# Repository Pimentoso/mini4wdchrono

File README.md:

# Mini4wdChrono

Mini4wdChrono is a free, open-source desktop application for timing and managing
Mini 4WD races on three-lane Japan Cup tracks. It combines Arduino-based lap
detection with an interface designed for race organizers and large-screen displays.

## Features

- Live timing for up to three lanes, including position, gaps, average speed, and split times
- Configurable lap counts, timing thresholds, start sequence, sensors, LEDs, and buzzer
- Track import from [Mini4WD Track Editor](https://mini4wd-track-editor.pimentoso.com/)
- Player and round import from [Mini4WD Tournament Generator](https://mini4wd-tournament.pimentoso.com/)
- Tournament standings, editable results, and free-race support
- Persistent race data and Excel result exports

## Hardware

The hardware is designed to be affordable and straightforward to assemble while
maintaining accurate timing. An Arduino running Firmata connects the sensors and
optional start button, LED strip, and buzzer to the application.

See the project wiki for complete assembly and setup instructions:

- [Required hardware](https://github.com/Pimentoso/mini4wdchrono/wiki/Hardware-parts-needed)
- [Wiring diagrams](https://github.com/Pimentoso/mini4wdchrono/wiki/Hardware-diagrams)
- [Flashing the Arduino](https://github.com/Pimentoso/mini4wdchrono/wiki/Flashing-the-arduino-board)
- [Building the lap timer](https://github.com/Pimentoso/mini4wdchrono/wiki/Lap-timer-building)
- [Launching the software](https://github.com/Pimentoso/mini4wdchrono/wiki/Launching-the-software)

## Download

Download a packaged build for your operating system from the
[GitHub Releases page](https://github.com/Pimentoso/mini4wdchrono/releases).
Available platforms may vary by release.

## Getting started

1. Build and flash the Arduino hardware by following the
   [hardware guides](https://github.com/Pimentoso/mini4wdchrono/wiki).
2. Connect the Arduino to your computer over USB.
3. Launch Mini4wdChrono and open the **Configuration** tab.
4. Select the serial port and configure the sensor pins and any optional hardware.
5. Create a track with
   [Mini4WD Track Editor](https://mini4wd-track-editor.pimentoso.com/) and load its
   link in the race setup screen.
6. For tournament races, create a player list and rounds with
   [Mini4WD Tournament Generator](https://mini4wd-tournament.pimentoso.com/) and
   load its link as well.

For more detail, see the
[software quick-start guide](https://github.com/Pimentoso/mini4wdchrono/wiki/Software-quick-start-guide)
and [tournament rules](https://github.com/Pimentoso/mini4wdchrono/wiki/Software-tournament-rules).

## Screenshots

### Live race view

Position, gap to the leader, average speed, and split times.

### Player standings

Player rankings with each racer's best time highlighted.

### Tournament rounds

An overview of every round with editable results.

### Race setup

Track, tournament, timing, and race-mode configuration.

## Development

Mini4wdChrono requires Node.js 22.13.0 and npm 9 or later. Node.js is managed
with [asdf](https://asdf-vm.com/); install asdf and its Node.js plugin, then
run the following from the repository root to install the pinned version:

```bash
asdf plugin add nodejs
asdf install
```

Use the setup instructions for your operating system before installing the
project.

### Set up macOS

Install the Xcode Command Line Tools, then install
[Homebrew](https://brew.sh/) if it is not already available:

```bash
xcode-select --install
```

After the Command Line Tools installation completes, use Homebrew to install
Git and the Arduino IDE:

```bash
brew install git
brew install --cask arduino-ide
```

### Set up Windows

Run the following commands from an elevated PowerShell window. They install Git,
Python, the Visual C++ build tools required by native dependencies, and the
Arduino IDE:

```powershell
winget install --id Git.Git --exact --accept-package-agreements --accept-source-agreements
winget install --id Python.Python.3.11 --exact --accept-package-agreements --accept-source-agreements
winget install --id Microsoft.VisualStudio.2022.BuildTools --exact `
  --accept-package-agreements --accept-source-agreements `
  --override "--wait --passive --add Microsoft.VisualStudio.Workload.VCTools --includeRecommended"
winget install --id ArduinoSA.IDE.stable --exact --accept-package-agreements --accept-source-agreements
winget install --id OpenJS.NodeJS.22 --exact --accept-package-agreements --accept-source-agreements
```

Close and reopen PowerShell after the installations finish so the new commands
are available on `PATH`.

### Set up Linux

The following commands prepare an Ubuntu or Debian system. They install the
compiler toolchain, Git, and zip:

```bash
sudo apt update
sudo apt install -y build-essential ca-certificates curl git zip
sudo usermod -aG dialout "$USER"
```

Sign out and back in after adding your account to the `dialout` group. This
allows Mini4wdChrono to access the Arduino serial port without making the device
world-writable. Install the [Arduino IDE](https://www.arduino.cc/en/software)
from Arduino's official download if you need to flash the board.

For other Linux distributions, install equivalent packages with the system's
package manager.

### Install and run Mini4wdChrono

After preparing the operating system, clone the repository, install the locked
dependencies, and start Electron:

```bash
git clone https://github.com/Pimentoso/mini4wdchrono.git
cd mini4wdchrono
npm ci
npm start
```

Connect a Firmata-compatible Arduino over USB to test hardware integration.
Use `npm run watch` to reload the application while developing. Run the linter
before submitting changes:

```bash
npm run lint:fix
npm run lint
```

### Project structure

- `window.js` — Electron main process, persistence, serial hardware, and IPC
- `preload.js` — restricted renderer-facing IPC API
- `js/` — renderer UI and race-management logic
- `index.html` — application markup
- `utils/` — release packaging scripts

## Building release artifacts

The build scripts install the locked dependencies, package the application, and
create a zip file in `release-builds/`.

| Platform | Command | Output |
| --- | --- | --- |
| macOS x64 | `./utils/build-darwin.sh` | `Mini4wdChrono-mac-x64.zip` |
| Linux x64 | `./utils/build-linux-x64.sh` | `Mini4wdChrono-linux-x64.zip` |
| Windows x64 | `.\utils\build-win64.ps1` | `Mini4wdChrono-windows-x64.zip` |

Run each script on its target operating system. Cross-platform packaging is not
supported by these scripts.

## Contributing

Bug reports and pull requests are welcome. Before opening a pull request:

1. Create a focused branch for the change.
2. Keep hardware access in the Electron main process and expose it to the
   renderer through IPC.
3. Run `npm run lint:fix` followed by `npm run lint`.
4. Describe the change, how it was tested, and any hardware used for testing.

Please use [GitHub Issues](https://github.com/Pimentoso/mini4wdchrono/issues) for bugs and feature requests.

## License

Mini4wdChrono is available under the [MIT License](LICENSE).

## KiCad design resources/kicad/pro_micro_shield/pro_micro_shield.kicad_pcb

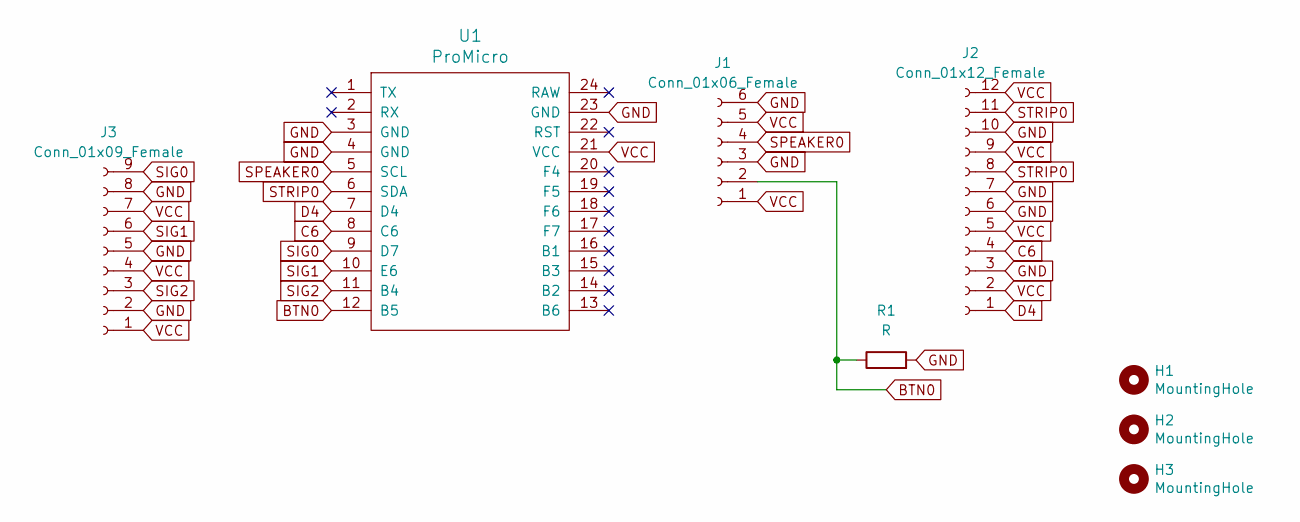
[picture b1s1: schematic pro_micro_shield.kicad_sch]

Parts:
H1, H2, H3: MountingHole; MountingHole_2.2mm_M2
J1: Conn_01x06_Female; PinHeader_1x06_P2.54mm_Vertical
J2: Conn_01x12_Female; PinHeader_1x12_P2.54mm_Vertical
J3: Conn_01x09_Female; PinHeader_1x09_P2.54mm_Vertical
R1: R; R_Axial_DIN0207_L6.3mm_D2.5mm_P15.24mm_Horizontal
U1: ProMicro; ArduinoProMicro

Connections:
BTN0: J1.2, R1.1, U1.12 (B5)
C6: J2.4, U1.8 (C6)
D4: J2.1, U1.7 (D4)
GND: J1.3, J1.6, J2.3, J2.6, J2.7, J2.10, J3.2, J3.5, J3.8, R1.2, U1.3 (GND), U1.4 (GND), U1.23 (GND)
SIG0: J3.9, U1.9 (D7)
SIG1: J3.6, U1.10 (E6)
SIG2: J3.3, U1.11 (B4)
SPEAKER0: J1.4, U1.5 (SCL)
STRIP0: J2.8, J2.11, U1.6 (SDA)
VCC: J1.1, J1.5, J2.2, J2.5, J2.9, J2.12, J3.1, J3.4, J3.7, U1.21 (VCC)

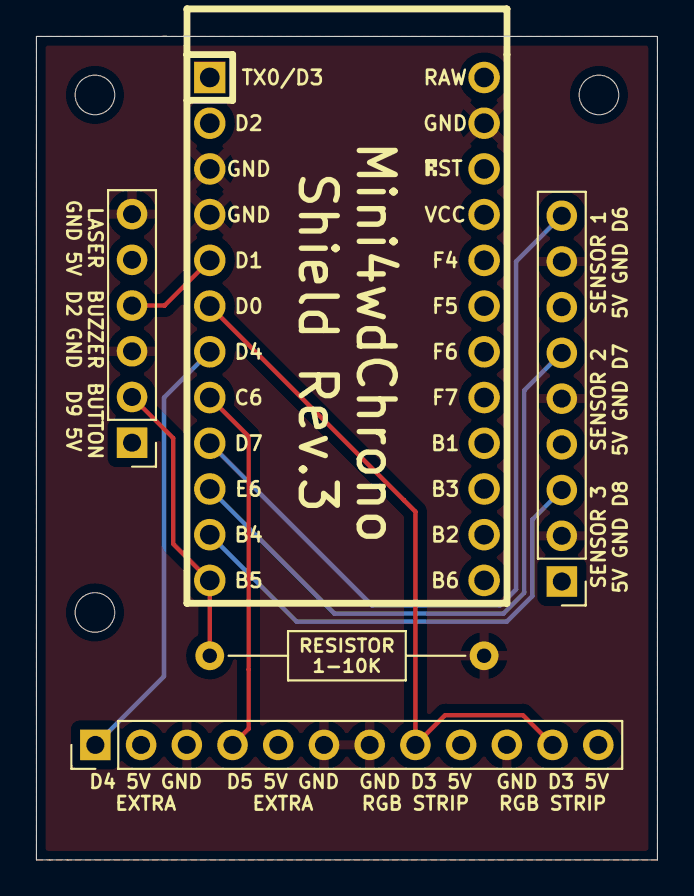
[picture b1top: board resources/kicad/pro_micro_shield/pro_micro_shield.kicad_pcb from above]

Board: 2 copper layers, 34.5 x 45.8 mm, 8 parts (0 on the bottom side), 10 nets.

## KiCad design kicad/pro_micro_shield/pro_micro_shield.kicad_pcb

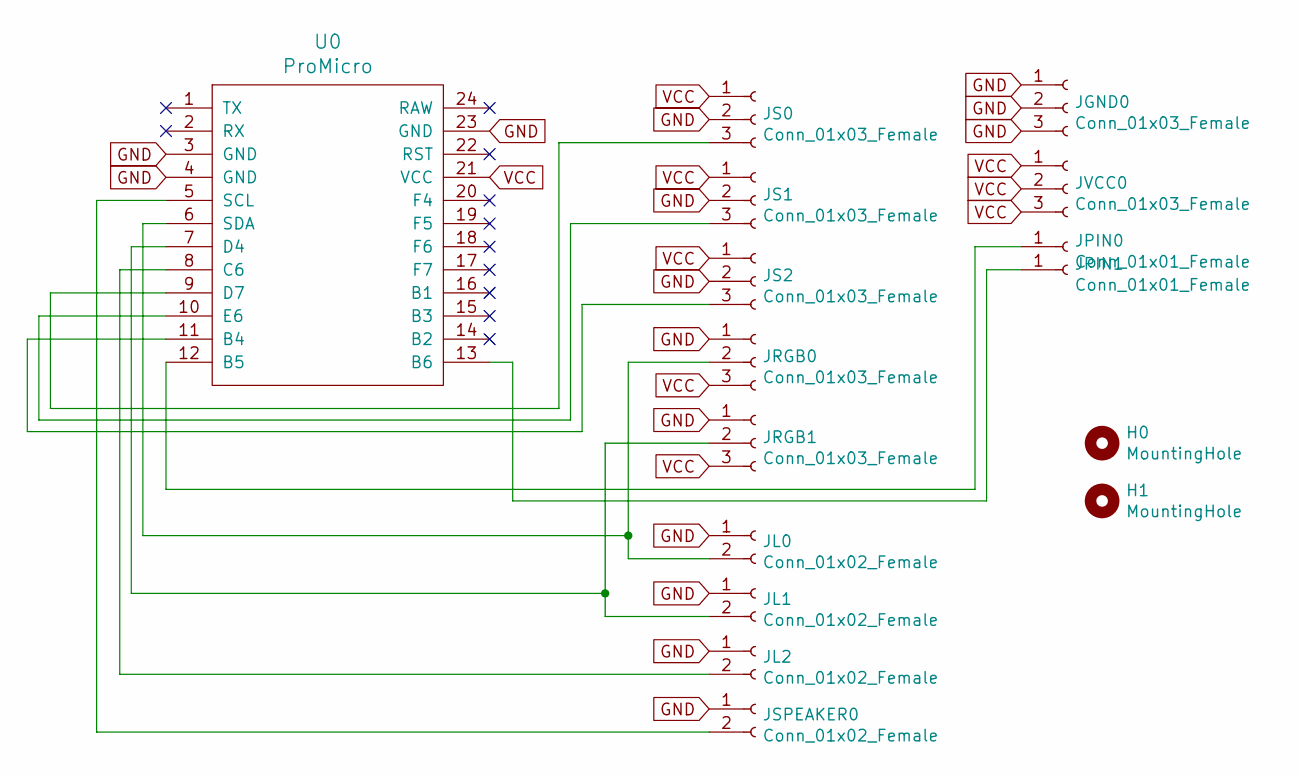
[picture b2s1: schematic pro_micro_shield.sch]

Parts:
H0, H1: MountingHole; MountingHole_2.2mm_M2
JGND0: Conn_01x03_Female; SolderWirePad_1x03_P3.175mm_Drill1mm
JL0, JL1, JL2: Conn_01x02_Female; SolderWirePad_1x02_P3.81mm_Drill1mm
JPIN0, JPIN1: Conn_01x01_Female; SolderWirePad_1x01_Drill1mm
JRGB0, JRGB1: Conn_01x03_Female; SolderWirePad_1x03_P3.175mm_Drill1mm
JS0, JS1, JS2: Conn_01x03_Female; SolderWirePad_1x03_P3.175mm_Drill1mm
JSPEAKER0: Conn_01x02_Female; SolderWirePad_1x02_P3.81mm_Drill1mm
JVCC0: Conn_01x03_Female; SolderWirePad_1x03_P3.175mm_Drill1mm
U0: ProMicro; ArduinoProMicro

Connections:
GND: JGND0.1, JGND0.2, JGND0.3, JL0.1, JL1.1, JL2.1, JRGB0.1, JRGB1.1, JS0.2, JS1.2, JS2.2, JSPEAKER0.1, U0.3 (GND), U0.4 (GND), U0.23 (GND)
unnamed: JL0.2, JRGB0.2, U0.6 (SDA)
unnamed: JL1.2, JRGB1.2, U0.7 (D4)
unnamed: JL2.2, U0.8 (C6)
unnamed: JPIN0.1, U0.12 (B5)
unnamed: JPIN1.1, U0.13 (B6)
unnamed: JS0.3, U0.9 (D7)
unnamed: JS1.3, U0.10 (E6)
unnamed: JS2.3, U0.11 (B4)
unnamed: JSPEAKER0.2, U0.5 (SCL)
VCC: JRGB0.3, JRGB1.3, JS0.1, JS1.1, JS2.1, JVCC0.1, JVCC0.2, JVCC0.3, U0.21 (VCC)

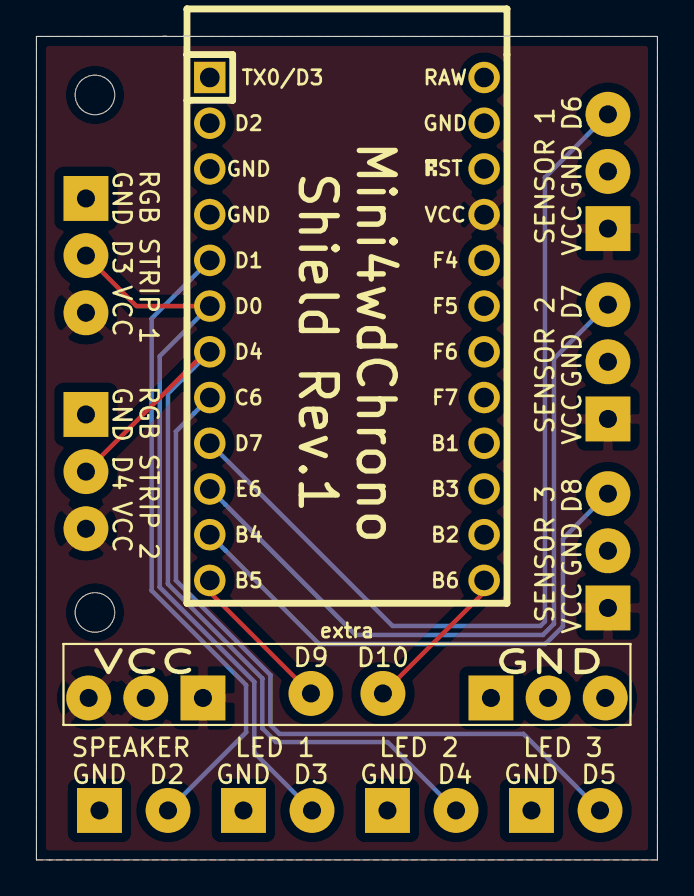
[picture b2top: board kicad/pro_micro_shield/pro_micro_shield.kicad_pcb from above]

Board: 2 copper layers, 34.5 x 45.8 mm, 16 parts (0 on the bottom side), 11 nets.

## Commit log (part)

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2019-11-15 fix next round names
2019-11-15 translate invalidate button
2019-11-25 Led manager initialization and ui control
2019-11-30 fix LedManagerLilypad
2019-12-04 try to style player list a bit during print
2019-12-06 README
2019-12-30 add electron-settings dependency and refactor
2019-12-30 refactor
2020-01-08 fixed node version to 10.16.3
2020-01-10 toggle race setup UI elements on round end
2020-01-11 fix #22
2020-01-11 cleanup
2020-01-24 add open race button
2020-01-24 add modals
2020-01-26 load race modal wip
2020-01-28 update build scripts to use local electron-packager
2020-02-08 fix load race with modal links
2020-02-09 led manager fixes
2020-02-15 fix windows build script
2020-02-16 fix #45
2020-02-19 fix #49 (needs testing)
2020-02-24 set defaults when loading empty race files
2020-03-02 reset playerList when loading different tournament
2020-03-02 add mock ledmanager
2020-03-02 fix init playerTimes
2020-03-04 init stuff before tournamentLoadDone
2020-03-07 add shield kicad project
2020-03-08 cleanup shield kicad project and readme
2020-03-31 add delete race button
2020-03-31 add wiki links
2020-03-31 fix init order
2020-04-16 resources
2020-04-29 split led_manager into separate classes
2020-04-29 Bump jquery from 3.4.1 to 3.5.0
    Bumps [jquery](https://github.com/jquery/jquery) from 3.4.1 to 3.5.0.
    - [Release notes](https://github.com/jquery/jquery/releases)
    - [Commits](https://github.com/jquery/jquery/compare/3.4.1...3.5.0)
2020-05-16 singleton classes for led manager
2020-06-03 add optional label to tournament details, remove endurance mode
2020-06-15 bump version 0.13.1
    do not reset speed if car goes off track
    empty new race name field everytime the modal is opened
2020-07-16 migrate from electron-updater to electron-builder
2020-07-16 simplify and use native dialogs
2020-07-16 remove electron-rebuild
2020-07-16 add buildDependenciesFromSource = true
2020-07-16 Bump lodash from 4.17.15 to 4.17.19
    Bumps [lodash](https://github.com/lodash/lodash) from 4.17.15 to 4.17.19.
    - [Release notes](https://github.com/lodash/lodash/releases)
    - [Commits](https://github.com/lodash/lodash/compare/4.17.15...4.17.19)
2020-07-17 add --x64 flag to build
2020-07-17 build only against current platform (win32 builds from mac don't work because of native dependencies)
2020-07-17 remove check for updates button
2020-07-17 autoupdater logging
2020-07-17 bump version 0.14.4
2020-09-12 Bump lodash from 4.17.15 to 4.17.20
    Bumps [lodash](https://github.com/lodash/lodash) from 4.17.15 to 4.17.20.
    - [Release notes](https://github.com/lodash/lodash/releases)
    - [Commits](https://github.com/lodash/lodash/compare/4.17.15...4.17.20)
2020-09-12 Bump electron from 5.0.6 to 7.2.4
    Bumps [electron](https://github.com/electron/electron) from 5.0.6 to 7.2.4.
    - [Release notes](https://github.com/electron/electron/releases)
    - [Changelog](https://github.com/electron/electron/blob/master/docs/breaking-changes.md)
    - [Commits](https://github.com/electron/electron/compare/v5.0.6...v7.2.4)
2020-09-14 wip remote spreadsheet function
2020-09-14 add device name to USB port list if available
2020-09-23 add TOS file
2020-09-23 add PRIVACY file
2020-09-26 update css library, renew some interface parts and text, fix #42
2020-09-27 update screenshots in readme
2020-09-28 fix #62
2020-10-04 Fix free round disabling tournament input Fix UI refresh after times override
2020-10-21 add phisical button support
2020-10-21 start button pin configuration
2020-10-22 shield pcb revision 2
2020-11-01 update gerber for shield
2020-11-04 modals refactor
2020-12-09 bump version 0.13.5
2020-12-12 cleanup resources and shield gerber files
2021-02-21 fix #69
2021-02-22 fixes
2021-02-22 add speed in split times
2021-02-24 Add round laps setting (#71)
    * fix #69
    * fix ui
    * fixes
    * add speed in split times
    * fixes
2021-02-24 Bump bl from 1.2.2 to 1.2.3
    Bumps [bl](https://github.com/rvagg/bl) from 1.2.2 to 1.2.3.
    - [Release notes](https://github.com/rvagg/bl/releases)
    - [Commits](https://github.com/rvagg/bl/compare/v1.2.2...v1.2.3)
2021-02-28 check for cars running for more than 99.999
2021-03-12 Bump bl from 1.2.2 to 1.2.3 (#66)
    Bumps [bl](https://github.com/rvagg/bl) from 1.2.2 to 1.2.3.
    - [Release notes](https://github.com/rvagg/bl/releases)
    - [Commits](https://github.com/rvagg/bl/compare/v1.2.2...v1.2.3)
2021-03-12 Bump ini from 1.3.5 to 1.3.8 (#73)
    Bumps [ini](https://github.com/isaacs/ini) from 1.3.5 to 1.3.8.
    - [Release notes](https://github.com/isaacs/ini/releases)
    - [Commits](https://github.com/isaacs/ini/compare/v1.3.5...v1.3.8)
2021-03-17 fixed led manager for more than 3 laps
    removed led manager reference in configuration
2021-03-20 Random green light delay in final mode
2021-05-03 Bump y18n from 3.2.1 to 3.2.2 (#74)
    Bumps [y18n](https://github.com/yargs/y18n) from 3.2.1 to 3.2.2.
    - [Release notes](https://github.com/yargs/y18n/releases)
    - [Changelog](https://github.com/yargs/y18n/blob/master/CHANGELOG.md)
    - [Commits](https://github.com/yargs/y18n/commits)
2021-05-03 Bump electron from 5.0.13 to 9.4.0 (#68)
    Bumps [electron](https://github.com/electron/electron) from 5.0.13 to 9.4.0.
    - [Release notes](https://github.com/electron/electron/releases)
    - [Changelog](https://github.com/electron/electron/blob/master/docs/breaking-changes.md)
    - [Commits](https://github.com/electron/electron/compare/v5.0.13...v9.4.0)
2021-05-06 Bump yargs-parser from 13.1.1 to 13.1.2
    Bumps [yargs-parser](https://github.com/yargs/yargs-parser) from 13.1.1 to 13.1.2.
    - [Release notes](https://github.com/yargs/yargs-parser/releases)
    - [Changelog](https://github.com/yargs/yargs-parser/blob/master/docs/CHANGELOG-full.md)
    - [Commits](https://github.com/yargs/yargs-parser/commits)
2021-05-06 Bump underscore from 1.9.1 to 1.12.1
    Bumps [underscore](https://github.com/jashkenas/underscore) from 1.9.1 to 1.12.1.
    - [Release notes](https://github.com/jashkenas/underscore/releases)
    - [Commits](https://github.com/jashkenas/underscore/compare/1.9.1...1.12.1)
2021-05-09 Bump hosted-git-info from 2.7.1 to 2.8.9
    Bumps [hosted-git-info](https://github.com/npm/hosted-git-info) from 2.7.1 to 2.8.9.
    - [Release notes](https://github.com/npm/hosted-git-info/releases)
    - [Changelog](https://github.com/npm/hosted-git-info/blob/v2.8.9/CHANGELOG.md)
    - [Commits](https://github.com/npm/hosted-git-info/compare/v2.7.1...v2.8.9)
2021-06-05 use standard 2.54mm header pins in arduino shield
2021-06-10 Bump normalize-url from 4.3.0 to 4.5.1
    Bumps [normalize-url](https://github.com/sindresorhus/normalize-url) from 4.3.0 to 4.5.1.
    - [Release notes](https://github.com/sindresorhus/normalize-url/releases)
    - [Commits](https://github.com/sindresorhus/normalize-url/commits)
    ---
    updated-dependencies:
    - dependency-name: normalize-url
2021-06-23 fix #80
2021-08-03 Bump tar from 4.4.13 to 4.4.15
    Bumps [tar](https://github.com/npm/node-tar) from 4.4.13 to 4.4.15.
    - [Release notes](https://github.com/npm/node-tar/releases)
    - [Changelog](https://github.com/npm/node-tar/blob/main/CHANGELOG.md)
    - [Commits](https://github.com/npm/node-tar/compare/v4.4.13...v4.4.15)
    ---
    updated-dependencies:
2021-08-10 Bump path-parse from 1.0.6 to 1.0.7
    Bumps [path-parse](https://github.com/jbgutierrez/path-parse) from 1.0.6 to 1.0.7.
    - [Release notes](https://github.com/jbgutierrez/path-parse/releases)
    - [Commits](https://github.com/jbgutierrez/path-parse/commits/v1.0.7)
    ---
    updated-dependencies:
    - dependency-name: path-parse
2021-08-23 remove focus from free round toggle button just for cosmetic reasons
2021-08-23 Goto round button (#81)
    * fix #80
    * ui translation
    * translation
    * remove focus from free round toggle button just for cosmetic reasons
2021-08-25 fixed postinstall and packager scripts
2021-08-26 goto round button is on newline
2021-08-29 Bump tar from 4.4.13 to 4.4.19
    Bumps [tar](https://github.com/npm/node-tar) from 4.4.13 to 4.4.19.
    - [Release notes](https://github.com/npm/node-tar/releases)
    - [Changelog](https://github.com/npm/node-tar/blob/main/CHANGELOG.md)
    - [Commits](https://github.com/npm/node-tar/compare/v4.4.13...v4.4.19)
    ---
    updated-dependencies:
2021-08-29 Bump lodash from 4.17.20 to 4.17.21
    Bumps [lodash](https://github.com/lodash/lodash) from 4.17.20 to 4.17.21.
    - [Release notes](https://github.com/lodash/lodash/releases)
    - [Commits](https://github.com/lodash/lodash/compare/4.17.20...4.17.21)
2022-03-25 Bump electron from 9.4.4 to 13.6.6
    Bumps [electron](https://github.com/electron/electron) from 9.4.4 to 13.6.6.
    - [Release notes](https://github.com/electron/electron/releases)
    - [Changelog](https://github.com/electron/electron/blob/main/docs/breaking-changes.md)
    - [Commits](https://github.com/electron/electron/compare/v9.4.4...v13.6.6)
    ---
    updated-dependencies:
2022-04-09 Bump moment from 2.24.0 to 2.29.2
    Bumps [moment](https://github.com/moment/moment) from 2.24.0 to 2.29.2.
    - [Release notes](https://github.com/moment/moment/releases)
    - [Changelog](https://github.com/moment/moment/blob/develop/CHANGELOG.md)
    - [Commits](https://github.com/moment/moment/compare/2.24.0...2.29.2)
    ---
    updated-dependencies:
2022-05-04 invert sensors 1 and 3
2022-05-04 add laneIndex method to led managers
2022-06-16 Bump electron from 9.4.4 to 15.5.5
    Bumps [electron](https://github.com/electron/electron) from 9.4.4 to 15.5.5.
    - [Release notes](https://github.com/electron/electron/releases)
    - [Changelog](https://github.com/electron/electron/blob/main/docs/breaking-changes.md)
    - [Commits](https://github.com/electron/electron/compare/v9.4.4...v15.5.5)
    ---
    updated-dependencies:
2022-06-28 Lane reverse option (#92)
    * invert sensors 1 and 3
    * add laneIndex method to led managers
    * add checkbox in config page
2022-06-29 fix serialport warning
2022-06-29 correctly handle reverse in led managers
2022-06-29 Bump plist from 3.0.4 to 3.0.5
    Bumps [plist](https://github.com/TooTallNate/node-plist) from 3.0.4 to 3.0.5.
    - [Release notes](https://github.com/TooTallNate/node-plist/releases)
    - [Changelog](https://github.com/TooTallNate/plist.js/blob/master/History.md)
    - [Commits](https://github.com/TooTallNate/node-plist/commits)
    ---
    updated-dependencies:
2022-07-04 fix double reverse of lap leds
2022-10-30 Make physical start button also stop a started race
2022-10-30 Make physical start button also stop a started race (#97)
2023-01-03 fix call to function
2023-01-27 update node-pixel dependency
2023-01-27 add hint to buzzer and start button pins in configuration
2023-02-01 shield revision 3
2023-02-03 reset pulldown option on button
2023-02-25 fix broken stuff from last commit
2023-03-26 update node and package
2023-03-26 fix stop race function
    # Conflicts:
    # js/storage.js
2023-03-27 fix dev tools window
2023-03-27 fix merge
2023-03-28 fix export addLap function
2023-04-01 add electron/remote dependency
2023-04-19 update requires to electron/remote
2023-04-23 refactor storage
2023-05-26 update j5 and serialport
2023-06-13 add strftime package
2023-06-13 rollback to electron-settings v3.2.0
2023-06-15 fix sum of best times
2023-06-15 code formatting
2023-06-22 copy relevant fixes from node18 branch
2023-06-23 fix getRecentFiles
2023-06-25 led managers methods
2023-06-27 Cleanup code - remove playerTimes variable (#98)
    * remove getPlayerList variable and add lib method to storage
    * fix broken stuff from last commit
    * fix stop race function
    * fix merge
    * copy relevant fixes from node18 branch
    * fix getRecentFiles
2023-06-27 fix player list on load
2023-06-27 updateUiState method
2023-06-30 Reload program after saving config (#101)
2023-06-30 Fix UI element visibility (#102)
    * fix player list on load
    * updateUiState method
    * fix element visibility
    * remove debugger
2023-07-06 led managers
2023-07-07 add options to RGB led manager
2023-07-19 Add "instant race start" option (#103)
    * remove getPlayerList variable and add lib method to storage
    * fix broken stuff from last commit
    * fix stop race function
    * fix merge
    * copy relevant fixes from node18 branch
    * fix getRecentFiles
2023-07-31 Added linux build commands
2023-08-20 add linux-x64 build script
2023-09-10 remove duplicate firmware
2024-08-01 update lockfile
2025-04-07 requirements file
2025-04-07 lint entire project
2025-06-08 eslint fixes
2026-01-10 step 0: planning
2026-01-10 fix postinstall.js typo
2026-01-25 step 2.1: file system ops
2026-01-25 step 2: done
2026-01-25 step 3: planning
2026-02-01 step 3: update serialport version
2026-02-01 step 3: done
2026-02-08 more eslint rules
2026-02-08 serialport list fix
2026-02-08 Initial plan
2026-02-08 AGENTS.md
2026-02-16 revert to raw digital read of pins
2026-02-16 revert to digiralWrite for the buzzer
2026-02-18 window.js cleanup
2026-02-26 fix macos build
2026-03-14 storage fixes
2026-04-13 cleanup and fix npm audit
2026-04-13 lint
2026-05-06 more eslint
2026-05-15 fix chrono
